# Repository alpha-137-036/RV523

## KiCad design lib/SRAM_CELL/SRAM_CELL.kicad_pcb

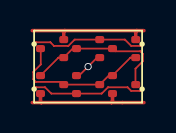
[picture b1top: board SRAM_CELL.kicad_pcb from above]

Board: 2 copper layers, 6 parts (0 on the bottom side), 5 nets.

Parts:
N1, N2, N3, N4: NMOS; SOT523
P1, P2: PMOS; SOT523

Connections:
GND: N1.2 (S), N2.2 (S)
Q: N1.3 (D), N2.1 (G), N3.3 (D), P1.3 (D), P2.1 (G)
Q_N: N1.1 (G), N2.3 (D), N4.3 (D), P1.1 (G), P2.3 (D)
VDD: P1.2 (S), P2.2 (S)
WL: N3.1 (G), N4.1 (G)

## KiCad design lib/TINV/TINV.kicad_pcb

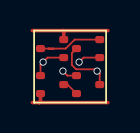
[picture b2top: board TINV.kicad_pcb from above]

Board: 2 copper layers, 4 parts (0 on the bottom side), 4 nets.

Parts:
N1, N2: NMOS; SOT523
P1, P2: PMOS; SOT523

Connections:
A: N1.1 (G), P1.1 (G)
Y: N2.3 (D), P2.3 (D)
intN: N1.3 (D), N2.2 (S)
intP: P1.3 (D), P2.2 (S)

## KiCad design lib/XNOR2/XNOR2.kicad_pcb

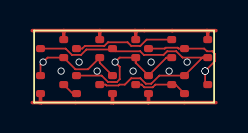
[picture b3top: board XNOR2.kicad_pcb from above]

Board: 2 copper layers, 10 parts (0 on the bottom side), 9 nets.

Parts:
N1, N2, N3, N4, N5: NMOS; SOT523
P1, P2, P3, P4, P5: PMOS; SOT523

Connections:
A: N1.1 (G), N3.1 (G), P1.1 (G), P3.1 (G)
B: N2.1 (G), N4.1 (G), P2.1 (G), P4.1 (G)
GND: N1.2 (S), N3.2 (S), N4.2 (S)
VDD: P1.2 (S), P2.2 (S), P3.2 (S), P5.2 (S)
Y: N5.3 (D), P4.3 (D), P5.3 (D)
inand: N2.3 (D), N5.1 (G), P1.3 (D), P2.3 (D), P5.1 (G)
nmid: N3.3 (D), N4.3 (D), N5.2 (S)
sndNA: N1.3 (D), N2.2 (S)
sndPA: P3.3 (D), P4.2 (S)
